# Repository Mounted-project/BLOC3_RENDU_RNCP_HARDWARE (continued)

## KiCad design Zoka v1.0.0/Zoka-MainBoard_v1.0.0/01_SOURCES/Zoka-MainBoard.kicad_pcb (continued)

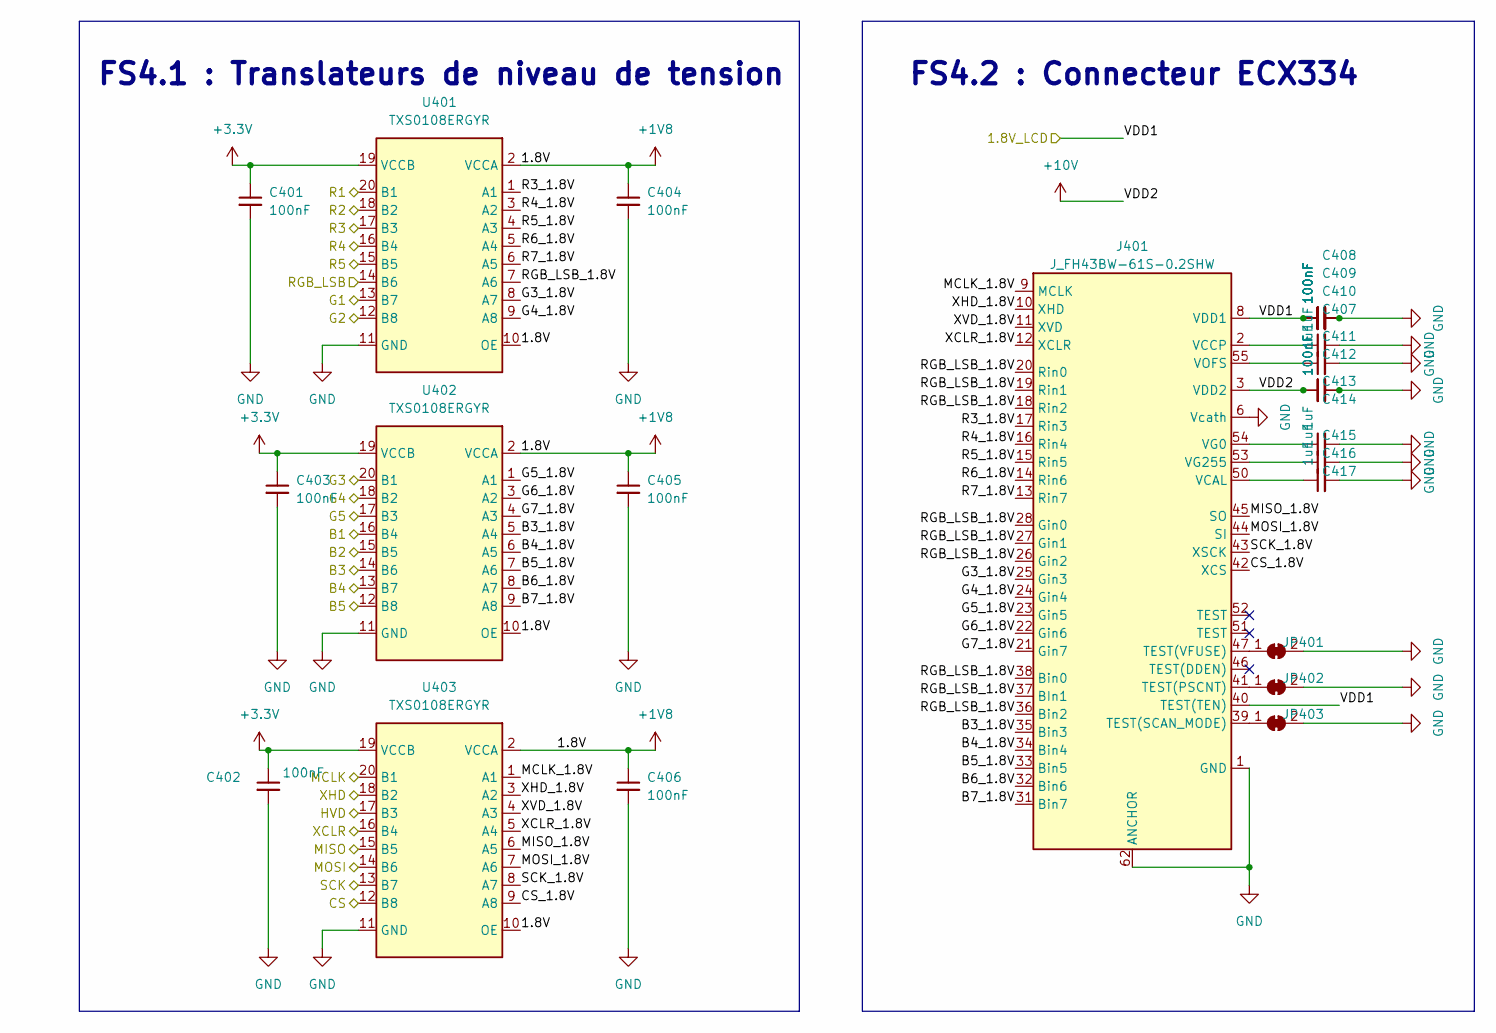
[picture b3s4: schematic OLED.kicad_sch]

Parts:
C401, C402, C403, C404, C405, C406, C407, C408, C409, C410, C413, C414: C_0603_100nF_100V_X7R_10%; C_0402_1005Metric; Voltage 50V; Tolerance 10%
C411, C412, C415, C416, C417: C_0402_1uF_10V_X7R_10%; C_0402_1005Metric; Voltage 10V; Tolerance 10%
J401: J_FH43BW-61S-0.2SHW; MPN FH43BW-61S-0.2SHW
JP401, JP402, JP403: SolderJumper_2_Bridged; SolderJumper-2_P1.3mm_Bridged_RoundedPad1.0x1.5mm
U401, U402, U403: U_TXS0108E; VQFN-20_TEXAS_INSTRUMENTS; MPN TXS0108ERGYR

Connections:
+1V8: C404.1, C405.1, C406.1, U401.2 (VCCA), U401.10 (OE), U402.2 (VCCA), U402.10 (OE), U403.2 (VCCA), U403.10 (OE); also elsewhere on the board
+3.3V: C401.1, C402.1, C403.1, U401.19 (VCCB), U402.19 (VCCB), U403.19 (VCCB); also elsewhere on the board
+10V: C413.1, C414.1, J401.3 (VDD2), J401.59 (VDD2); also elsewhere on the board
/1.8V_LCD: C407.1, C408.1, C409.1, C410.1, J401.8 (VDD1), J401.29 (VDD1), J401.40 (TEST(TEN)), J401.49 (VDD1); also elsewhere on the board
/B1: U402.16 (B4); also elsewhere on the board
/B2: U402.15 (B5); also elsewhere on the board
/B3: U402.14 (B6); also elsewhere on the board
/B4: U402.13 (B7); also elsewhere on the board
/B5: U402.12 (B8); also elsewhere on the board
/CS: U403.12 (B8); also elsewhere on the board
/G1: U401.13 (B7); also elsewhere on the board
/G2: U401.12 (B8); also elsewhere on the board
/G3: U402.20 (B1); also elsewhere on the board
/G4: U402.18 (B2); also elsewhere on the board
/G5: U402.17 (B3); also elsewhere on the board
/HVD: U403.17 (B3); also elsewhere on the board
/MCLK: U403.20 (B1); also elsewhere on the board
/MCU/RGB_LSB: U401.14 (B6); also elsewhere on the board
/MISO: U403.15 (B5); also elsewhere on the board
/MOSI: U403.14 (B6); also elsewhere on the board
/OLED/B3_1.8V: J401.35 (Bin3), U402.5 (A4)
/OLED/B4_1.8V: J401.34 (Bin4), U402.6 (A5)
/OLED/B5_1.8V: J401.33 (Bin5), U402.7 (A6)
/OLED/B6_1.8V: J401.32 (Bin6), U402.8 (A7)
/OLED/B7_1.8V: J401.31 (Bin7), U402.9 (A8)
/OLED/CS_1.8V: J401.42 (XCS), U403.9 (A8)
/OLED/G3_1.8V: J401.25 (Gin3), U401.8 (A7)
/OLED/G4_1.8V: J401.24 (Gin4), U401.9 (A8)
/OLED/G5_1.8V: J401.23 (Gin5), U402.1 (A1)
/OLED/G6_1.8V: J401.22 (Gin6), U402.3 (A2)
/OLED/G7_1.8V: J401.21 (Gin7), U402.4 (A3)
/OLED/MCLK_1.8V: J401.9 (MCLK), U403.1 (A1)
/OLED/MISO_1.8V: J401.45 (SO), U403.6 (A5)
/OLED/MOSI_1.8V: J401.44 (SI), U403.7 (A6)
/OLED/R3_1.8V: J401.17 (Rin3), U401.1 (A1)
/OLED/R4_1.8V: J401.16 (Rin4), U401.3 (A2)
/OLED/R5_1.8V: J401.15 (Rin5), U401.4 (A3)
/OLED/R6_1.8V: J401.14 (Rin6), U401.5 (A4)
/OLED/R7_1.8V: J401.13 (Rin7), U401.6 (A5)
/OLED/RGB_LSB_1.8V: J401.18 (Rin2), J401.19 (Rin1), J401.20 (Rin0), J401.26 (Gin2), J401.27 (Gin1), J401.28 (Gin0), J401.36 (Bin2), J401.37 (BIn1), J401.38 (Bin0), U401.7 (A6)
/OLED/SCK_1.8V: J401.43 (XSCK), U403.8 (A7)
/OLED/XCLR_1.8V: J401.12 (XCLR), U403.5 (A4)
/OLED/XHD_1.8V: J401.10 (XHD), U403.3 (A2)
/OLED/XVD_1.8V: J401.11 (XVD), U403.4 (A3)
/R1: U401.20 (B1); also elsewhere on the board
/R2: U401.18 (B2); also elsewhere on the board
/R3: U401.17 (B3); also elsewhere on the board
/R4: U401.16 (B4); also elsewhere on the board
/R5: U401.15 (B5); also elsewhere on the board
/SCK: U403.13 (B7); also elsewhere on the board
/XCLR: U403.16 (B4); also elsewhere on the board
/XHD: U403.18 (B2); also elsewhere on the board
GND: C401.2, C402.2, C403.2, C404.2, C405.2, C406.2, C407.2, C408.2, C409.2, C410.2, C411.2, C412.2, C413.2, C414.2, C415.2, C416.2, C417.2, J401.1 (GND), J401.4 (GND), J401.5 (GND), J401.6 (Vcath), J401.7 (GND), J401.30 (GND), J401.48 (GND), J401.56 (Vcath), J401.57 (GND), J401.58 (GND), J401.61 (GND), J401.62 (ANCHOR), J401.63 (ANCHOR), JP401.2 (B), JP402.2 (B), JP403.2 (B), U401.11 (GND), U402.11 (GND), U403.11 (GND); also elsewhere on the board
unnamed: C411.1, J401.2 (VCCP), J401.60 (VCCP)
unnamed: J401.41 (TEST(PSCNT)), JP402.1 (A)
unnamed: J401.39 (TEST(SCAN_MODE)), JP403.1 (A)
unnamed: J401.47 (TEST(VFUSE)), JP401.1 (A)
unnamed: C417.1, J401.50 (VCAL)
unnamed: C415.1, J401.54 (VG0)
unnamed: C416.1, J401.53 (VG255)
unnamed: C412.1, J401.55 (VOFS)

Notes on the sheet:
FS4.1 : Translateurs de niveau de tension
FS4.2 : Connecteur ECX334

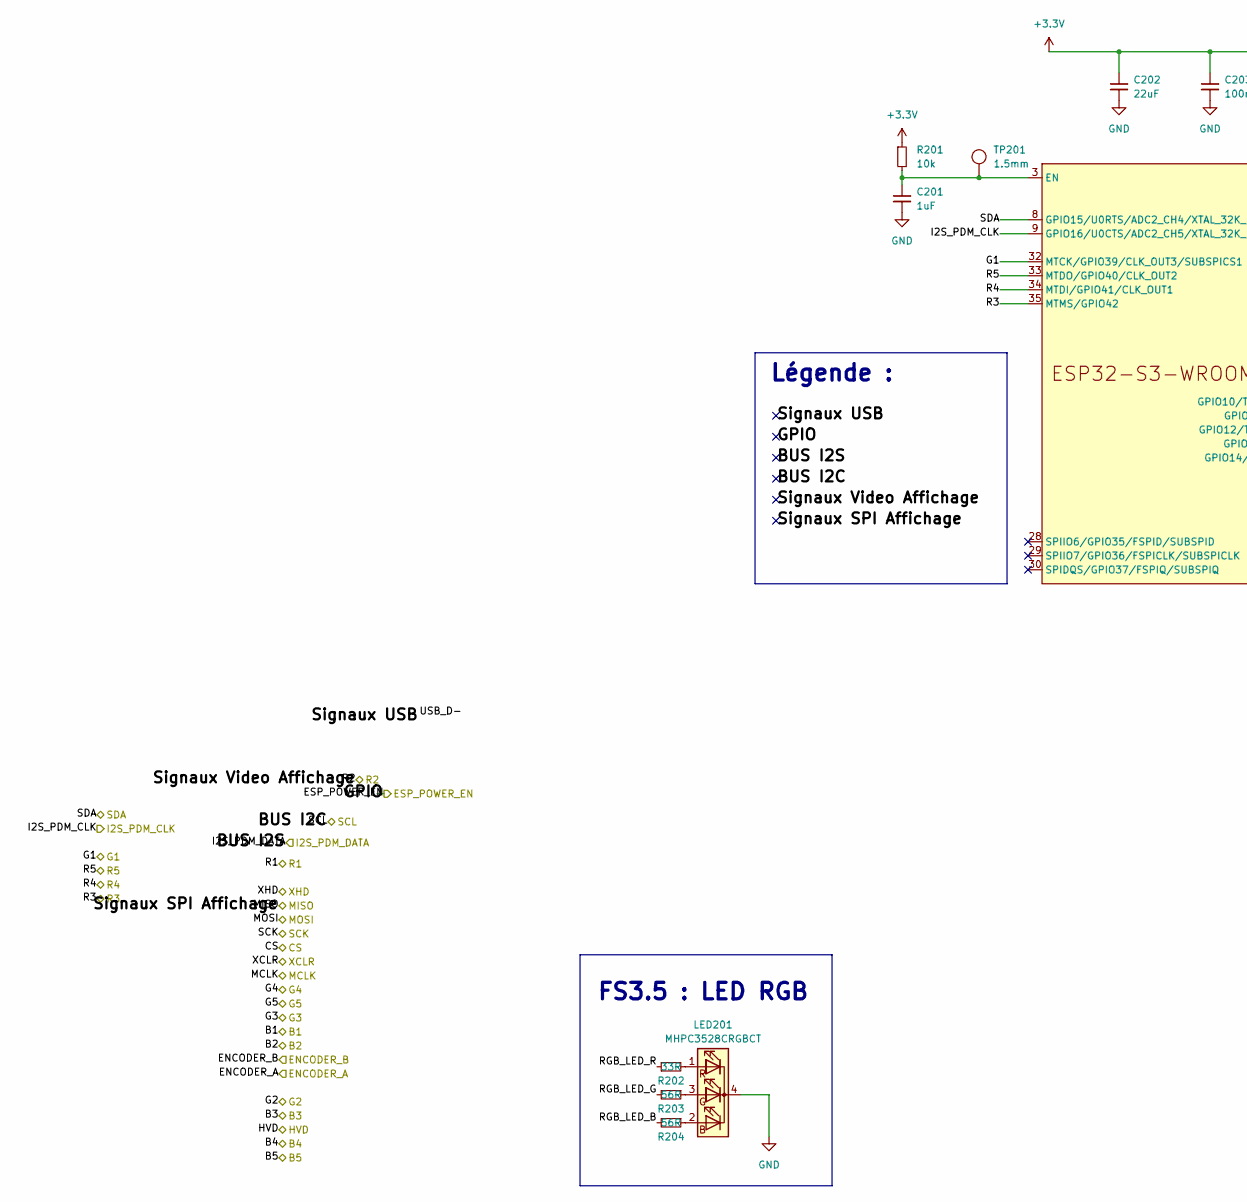
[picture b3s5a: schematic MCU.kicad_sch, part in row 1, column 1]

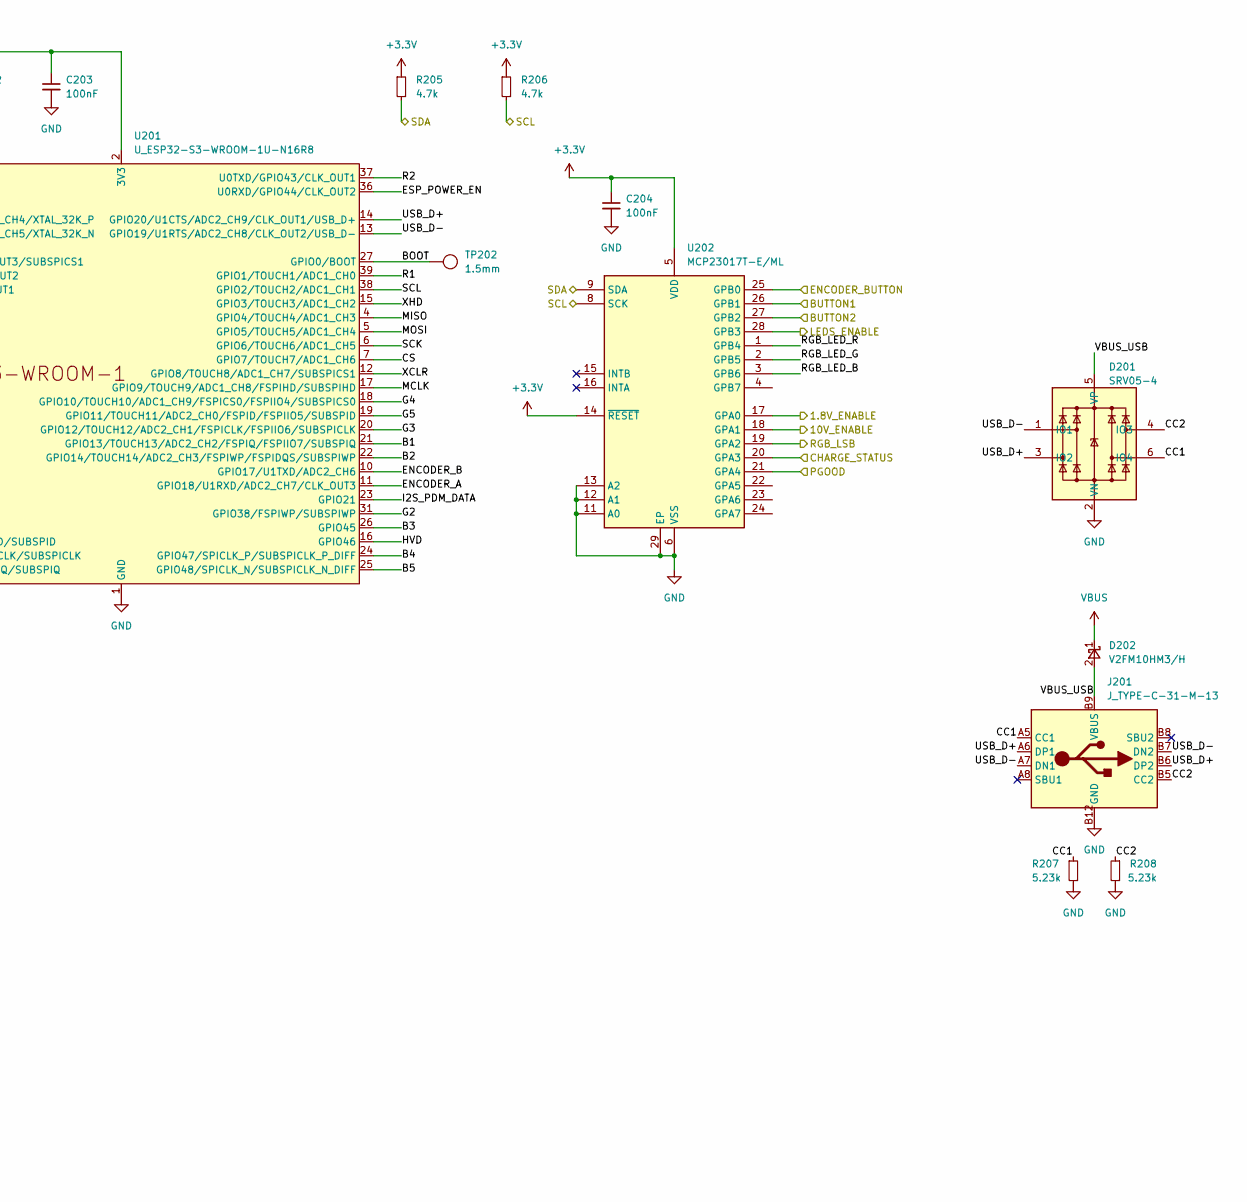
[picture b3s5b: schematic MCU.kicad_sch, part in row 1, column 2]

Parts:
C201: C_0402_1uF_10V_X7R_10%; C_0402_1005Metric; Voltage 10V; Tolerance 10%
C202: C_0805_22uF_10V_XR7_20%; C_0805_1608Metric; Voltage 10V; Tolerance 20%; PartStatus ___PartStatus
C203, C204: C_0603_100nF_100V_X7R_10%; C_0402_1005Metric; Voltage 50V; Tolerance 10%
D201: D_SRV05-4; SOT-23-6_TECH_PUBLIC; MPN SRV05-4
D202: D_V2FM10HM3/H; D_SMF_VISHAY; MPN V2FM10HM3/H
J201: J_TYPE-C-31-M-13; MPN TYPE-C-31-M-13
LED201: LED_MHPC3528CRGBCT; MPN MHPC3528CRGBCT
R201: R_0603_10k_1%_0.1W; R_0402_1005Metric; Tolerance 1%
R202: R_0402_33R_1%_0.06W; R_0402_1005Metric; Tolerance 1%
R203, R204: R_0402_56R_1%_0.06W; R_0402_1005Metric; Tolerance 1%
R205, R206: R_0603_4.7k_1%_0.1W; R_0402_1005Metric; Tolerance 1%
R207, R208: R_0603_5.23k_1%_0.1W; R_0402_1005Metric; Tolerance 1%
TP201, TP202: TESTPOINT_1.5MM
U201: ESP32-S3-WROOM-1U-N16R8; ESP32-S3-WROOM-1U; MPN ESP32-S3-WROOM-1U-N16R8
U202: U_MCP23017T-E/ML; QFN-28-1EP_6x6mm_P0.65mm_EP4.25x4.25mm_MICROCHIP; MPN MCP23017T-E/ML

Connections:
+3.3V: C202.1, C203.1, C204.1, R201.1, R205.1, R206.1, U201.2 (3V3), U202.5 (VDD), U202.14 (~RESET); also elsewhere on the board
/B1: U201.21 (GPIO13/TOUCH13/ADC2_CH2/FSPIQ/FSPIIO7/S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); also elsewhere on the board
/B2: U201.22 (GPIO14/TOUCH14/ADC2_CH3/FSPIWP/FSPIDQS/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); also elsewhere on the board
/B3: U201.26 (GPIO45); also elsewhere on the board
/B4: U201.24 (GPIO47/SPICLK_P/SUBSPICLK_P_DIFF); also elsewhere on the board
/B5: U201.25 (GPIO48/SPICLK_N/SUBSPICLK_N_DIFF); also elsewhere on the board
/BUTTON1: U202.26 (GPB1); also elsewhere on the board
/BUTTON2: U202.27 (GPB2); also elsewhere on the board
/Battery Management/1.8V_ENABLE: U202.17 (GPA0); also elsewhere on the board
/Battery Management/10V_ENABLE: U202.18 (GPA1); also elsewhere on the board
/Battery Management/CHARGE_STATUS: U202.20 (GPA3); also elsewhere on the board
/Battery Management/ENCODER_BUTTON: U202.25 (GPB0); also elsewhere on the board
/Battery Management/ESP_POWER_EN: U201.36 (U0RXD/GPIO44/CLK_OUT2); also elsewhere on the board
/Battery Management/PGOOD: U202.21 (GPA4); also elsewhere on the board
/CS: U201.7 (GPIO7/TOUCH7/ADC1_CH6); also elsewhere on the board
/ENCODER_A: U201.11 (GPIO18/U1RXD/ADC2_CH7/CLK_OUT3); also elsewhere on the board
/ENCODER_B: U201.10 (GPIO17/U1TXD/ADC2_CH6); also elsewhere on the board
/G1: U201.32 (MTCK/GPIO39/CLK_OUT3/SUBSPICS1); also elsewhere on the board
/G2: U201.31 (GPIO38/FSPIWP/SUBSPIWP); also elsewhere on the board
/G3: U201.20 (GPIO12/TOUCH12/ADC2_CH1/FSPICLK/FSPIIO6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); also elsewhere on the board
/G4: U201.18 (GPIO10/TOUCH10/ADC1_CH9/FSPICS0/FSPIIO4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); also elsewhere on the board
/G5: U201.19 (GPIO11/TOUCH11/ADC2_CH0/FSPID/FSPIIO5/S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); also elsewhere on the board
/HVD: U201.16 (GPIO46); also elsewhere on the board
/I2S_PDM_CLK: U201.9 (GPIO16/U0CTS/ADC2_CH5/XTAL_32K_N); also elsewhere on the board
/I2S_PDM_DATA: U201.23 (GPIO21); also elsewhere on the board
/LEDS_ENABLE: U202.28 (GPB3); also elsewhere on the board
/MCLK: U201.17 (GPIO9/TOUCH9/ADC1_CH8/FSPIHD/SUBSPIHD); also elsewhere on the board
/MCU/CC1: D201.6 (IO4), J201.A5 (CC1), R207.1
/MCU/CC2: D201.4 (IO3), J201.B5 (CC2), R208.1
/MCU/RGB_LED_B: R204.2, U202.3 (GPB6)
/MCU/RGB_LED_G: R203.2, U202.2 (GPB5)
/MCU/RGB_LED_R: R202.1, U202.1 (GPB4)
/MCU/RGB_LSB: U202.19 (GPA2); also elsewhere on the board
/MCU/USB_D+: D201.3 (IO2), J201.A6 (DP1), J201.B6 (DP2), U201.14 (GPIO20/U1CTS/ADC2_CH9/CLK_OUT1/USB_D+)
/MCU/USB_D-: D201.1 (IO1), J201.A7 (DN1), J201.B7 (DN2), U201.13 (GPIO19/U1RTS/ADC2_CH8/CLK_OUT2/USB_D-)
/MCU/VBUS_USB: D201.5 (VP), D202.2 (A), J201.A4 (VBUS), J201.A9 (VBUS), J201.B4 (VBUS), J201.B9 (VBUS)
/MISO: U201.4 (GPIO4/TOUCH4/ADC1_CH3); also elsewhere on the board
/MOSI: U201.5 (GPIO5/TOUCH5/ADC1_CH4); also elsewhere on the board
/R1: U201.39 (GPIO1/TOUCH1/ADC1_CH0); also elsewhere on the board
/R2: U201.37 (U0TXD/GPIO43/CLK_OUT1); also elsewhere on the board
/R3: U201.35 (MTMS/GPIO42); also elsewhere on the board
/R4: U201.34 (MTDI/GPIO41/CLK_OUT1); also elsewhere on the board
/R5: U201.33 (MTDO/GPIO40/CLK_OUT2); also elsewhere on the board
/SCK: U201.6 (GPIO6/TOUCH6/ADC1_CH5); also elsewhere on the board
/SCL: R206.2, U201.38 (GPIO2/TOUCH2/ADC1_CH1), U202.8 (SCK); also elsewhere on the board
/SDA: R205.2, U201.8 (GPIO15/U0RTS/ADC2_CH4/XTAL_32K_P), U202.9 (SDA); also elsewhere on the board
/XCLR: U201.12 (GPIO8/TOUCH8/ADC1_CH7/SUBSPICS1); also elsewhere on the board
/XHD: U201.15 (GPIO3/TOUCH3/ADC1_CH2); also elsewhere on the board
GND: C201.2, C202.2, C203.2, C204.2, D201.2 (VN), J201.A1 (GND), J201.A12 (GND), J201.B1 (GND), J201.B12 (GND), J201.GND, LED201.4 (K), R207.2, R208.2, U201.1 (GND), U201.40 (GND), U201.41 (GND), U202.6 (VSS), U202.11 (A0), U202.12 (A1), U202.13 (A2), U202.29 (EP); also elsewhere on the board
unnamed: LED201.3 (BA), R203.1
unnamed: LED201.2 (GA), R204.1
unnamed: LED201.1 (RA), R202.2
unnamed: C201.1, R201.2, TP201.1, U201.3 (EN)
unnamed: TP202.1, U201.27 (GPIO0/BOOT)
VBUS: D202.1 (K); also elsewhere on the board

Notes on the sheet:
FS3.5 : LED RGB
Légende :

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
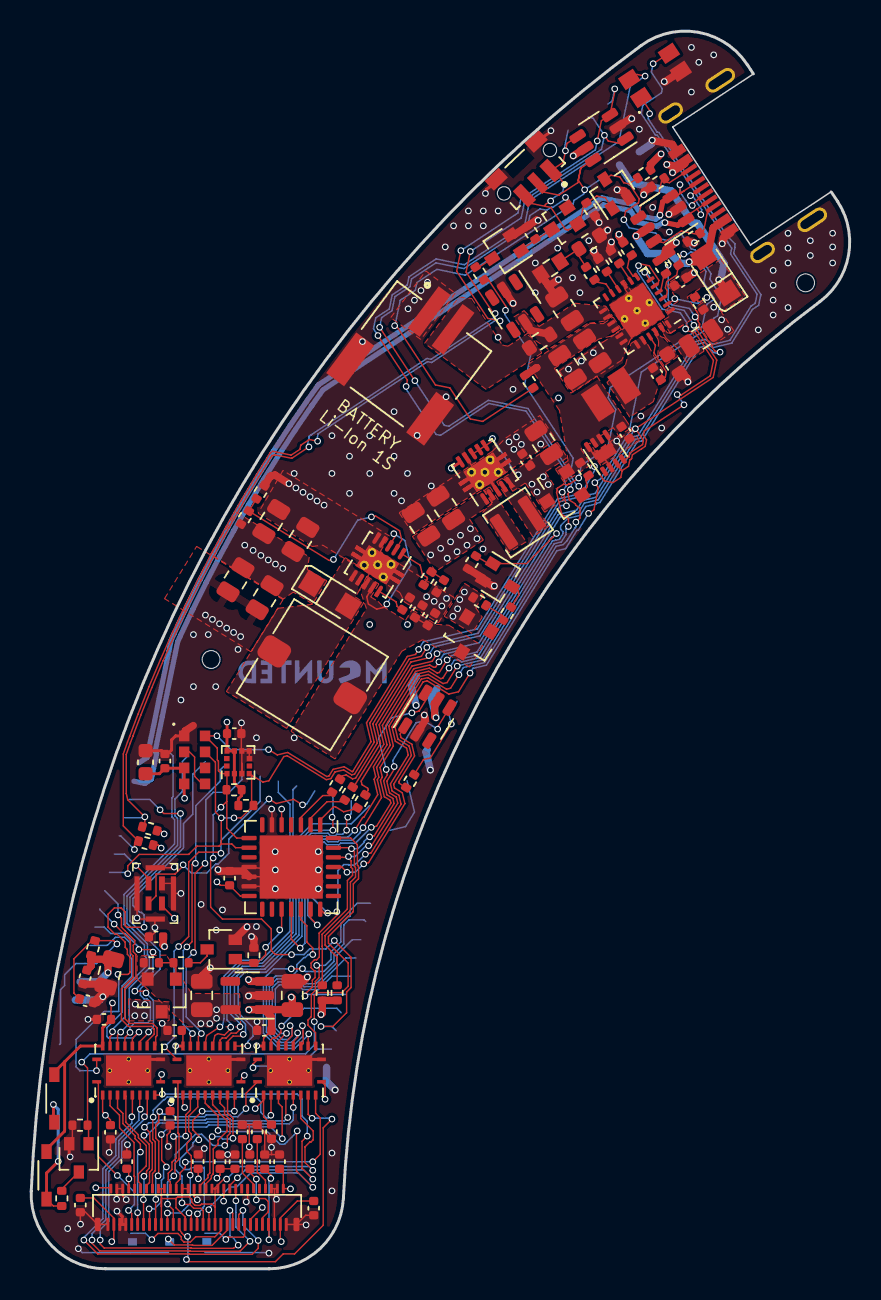
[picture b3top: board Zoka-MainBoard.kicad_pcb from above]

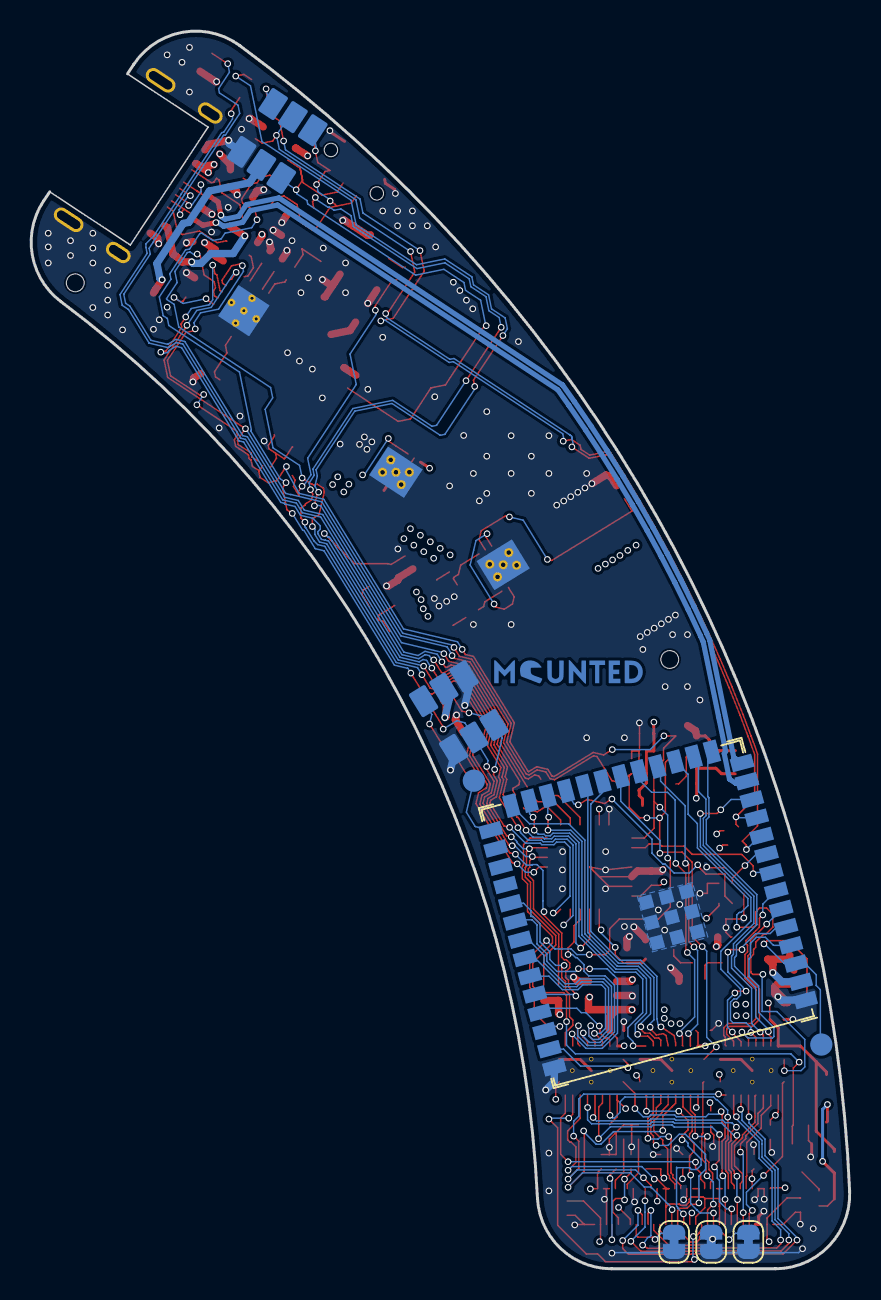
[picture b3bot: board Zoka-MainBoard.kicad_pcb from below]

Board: 4 copper layers, 55.1 x 83.3 mm, 135 parts (9 on the bottom side), 126 nets.

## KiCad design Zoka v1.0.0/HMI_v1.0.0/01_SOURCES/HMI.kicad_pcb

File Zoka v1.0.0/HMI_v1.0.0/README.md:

# CONFIDENTIAL

<p class="callout danger">The contents of this folder is confidential. Do not distribute outside of Gouach without permission.</p>

# CONTENT

This folder contains sub-folders with:
- RESOURCES -> All annex files that were useful in designing the board: DXF, datasheets...
- SOURCES -> Sources files of the board: KiCad project, schematic and layout files
- OUTPUTS -> All the files generated in KiCad: BOM, Gerbers, technical drawings, board 3D model...

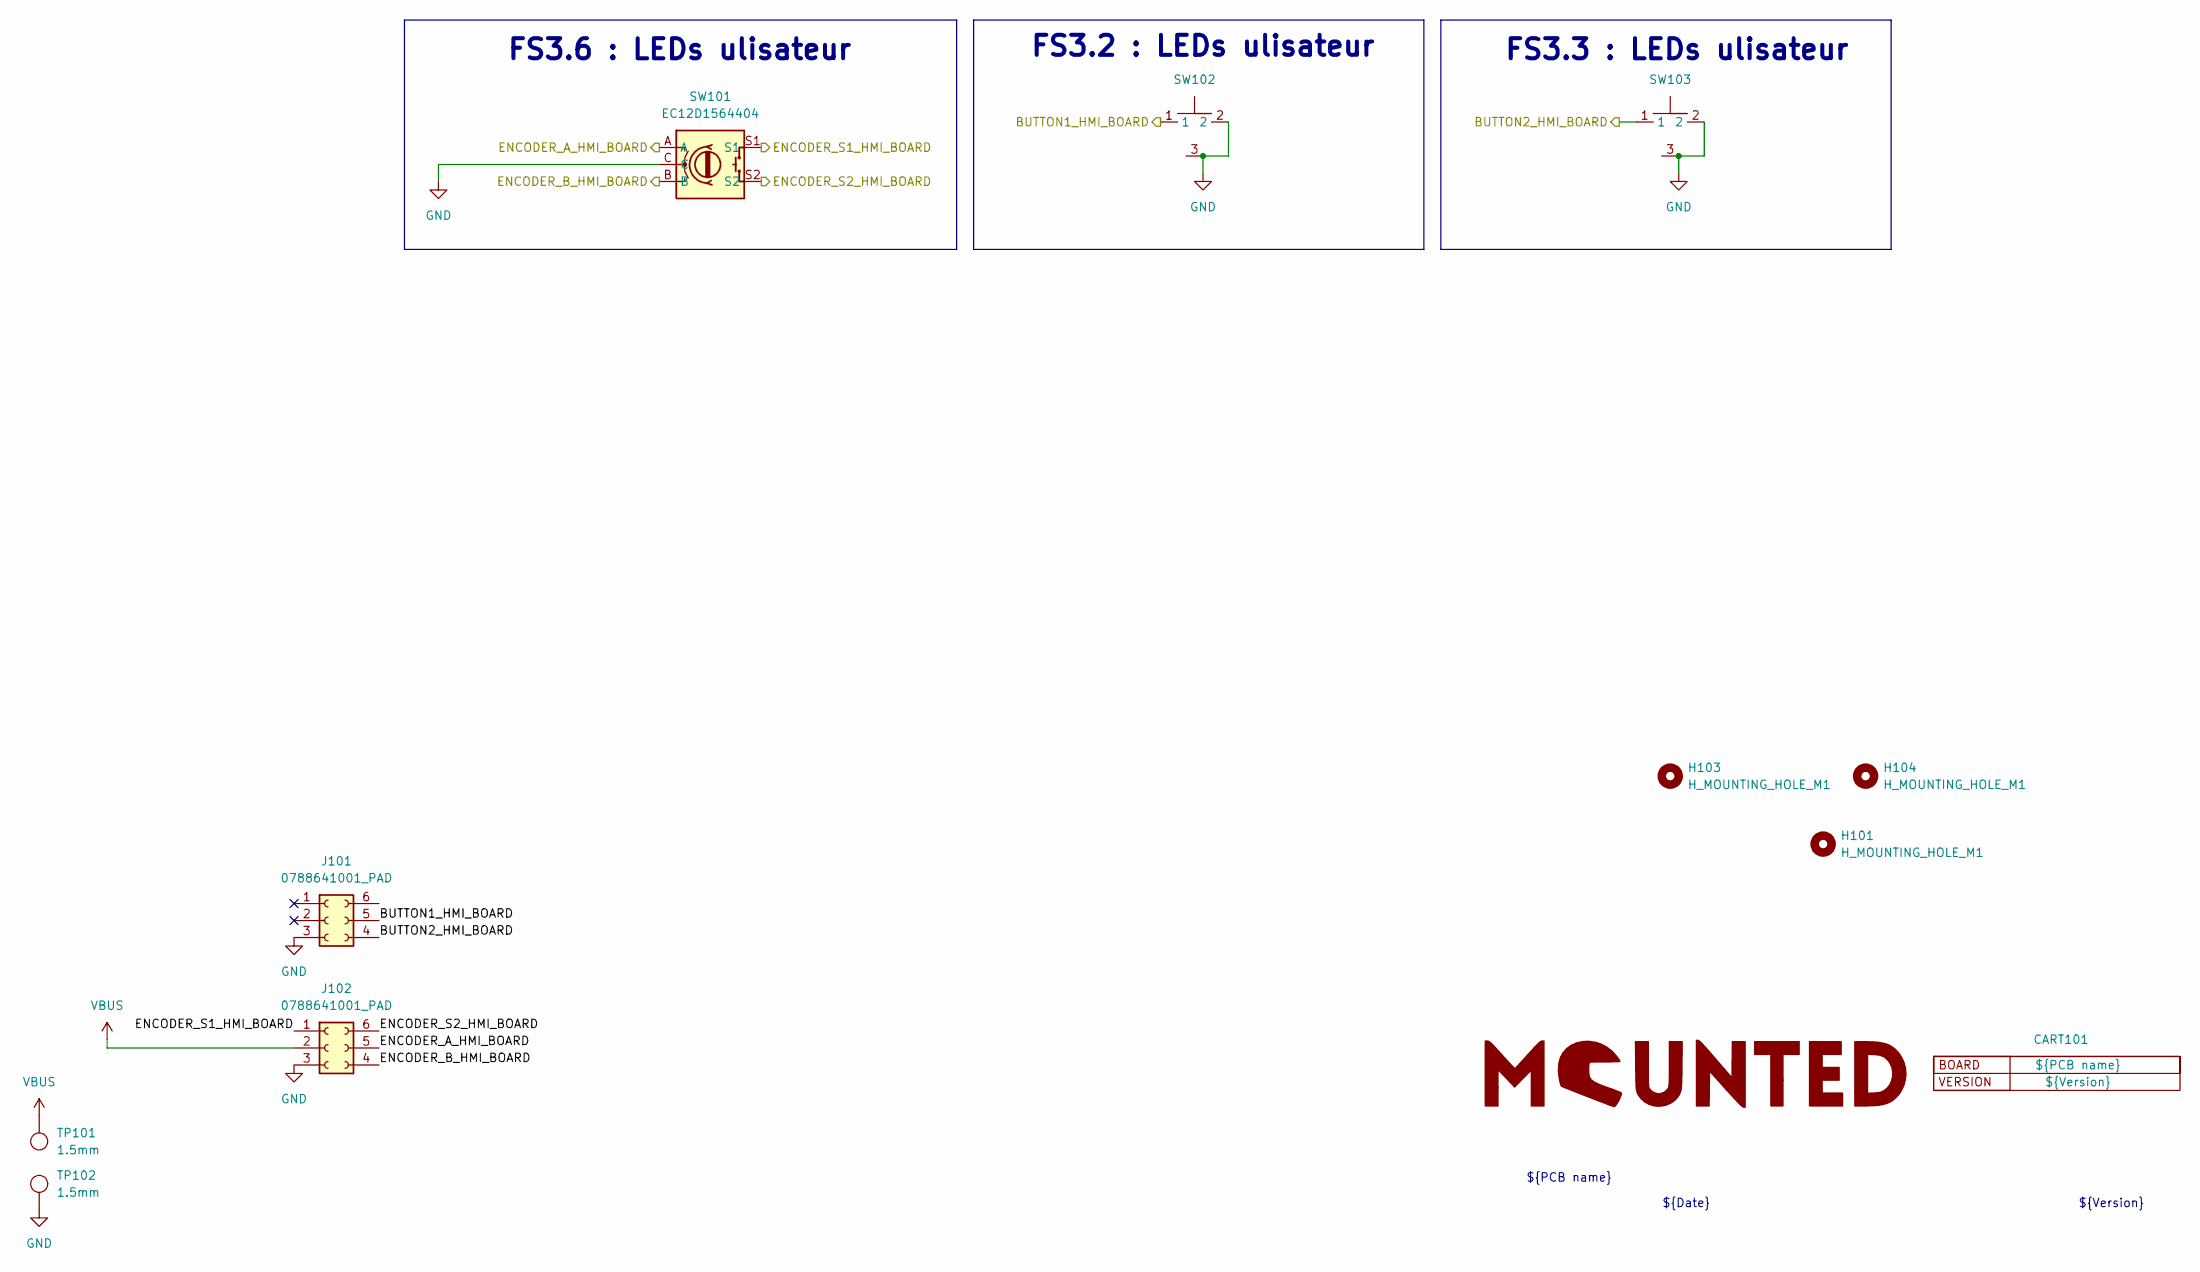
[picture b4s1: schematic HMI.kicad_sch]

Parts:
CART101: Cartouche_IO
H101, H103, H104: H_MOUNTING_HOLE_M1; MountingHole_1.2mm_M1
J101, J102: J_0788641001_PAD; J_788641001_PAD; MPN 0788641001
LOGO101: mounted_logo
SW101: SW_EC12D1564404; MPN EC12D1564404
SW102, SW103: SW_SKRTLAE010; MPN SKRTLAE010
TP101, TP102: TESTPOINT_1.5MM

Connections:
/BUTTON1_HMI_BOARD: J101.5, SW102.1
/BUTTON2_HMI_BOARD: J101.4, SW103.1
/ENCODER_A_HMI_BOARD: J102.5, SW101.A
/ENCODER_B_HMI_BOARD: J102.4, SW101.B
/ENCODER_S1_HMI_BOARD: J102.1, SW101.S1
/ENCODER_S2_HMI_BOARD: J102.6, SW101.S2
GND: J101.3, J102.3, SW101.C, SW102.2, SW102.3, SW103.2, SW103.3, TP102.1
VBUS: J102.2, TP101.1

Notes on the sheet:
${PCB name}
FS3.2 : LEDs ulisateur
FS3.6 : LEDs ulisateur
${Date}
FS3.3 : LEDs ulisateur
${Version}

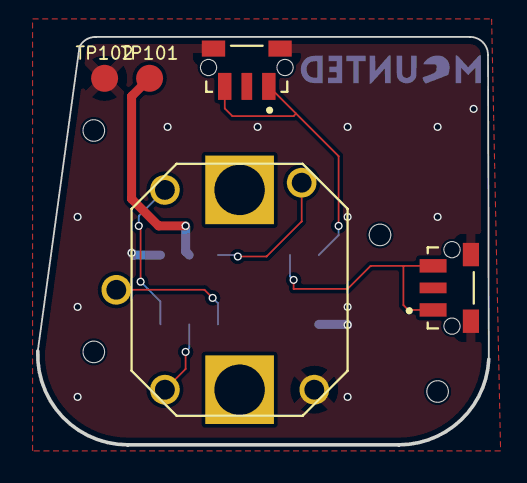
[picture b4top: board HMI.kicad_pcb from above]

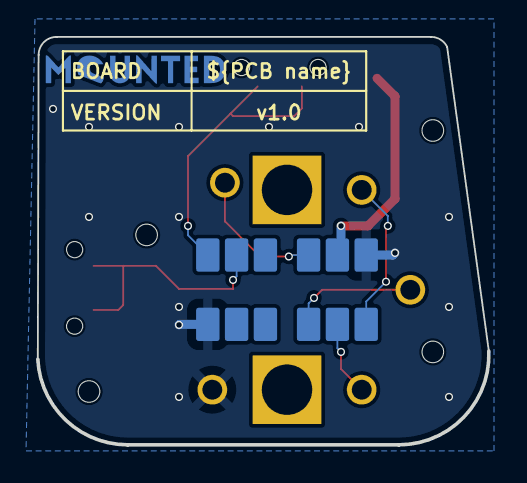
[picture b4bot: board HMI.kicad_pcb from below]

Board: 2 copper layers, 25.1 x 22.6 mm, 13 parts (4 on the bottom side), 8 nets.

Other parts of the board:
H104#2: H_MOUNTING_HOLE_M1; MountingHole_1.2mm_M1

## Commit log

2024-09-03 Rendu
